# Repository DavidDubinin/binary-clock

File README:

# BINARY CLOCK AVR CODE - ATMEGA48

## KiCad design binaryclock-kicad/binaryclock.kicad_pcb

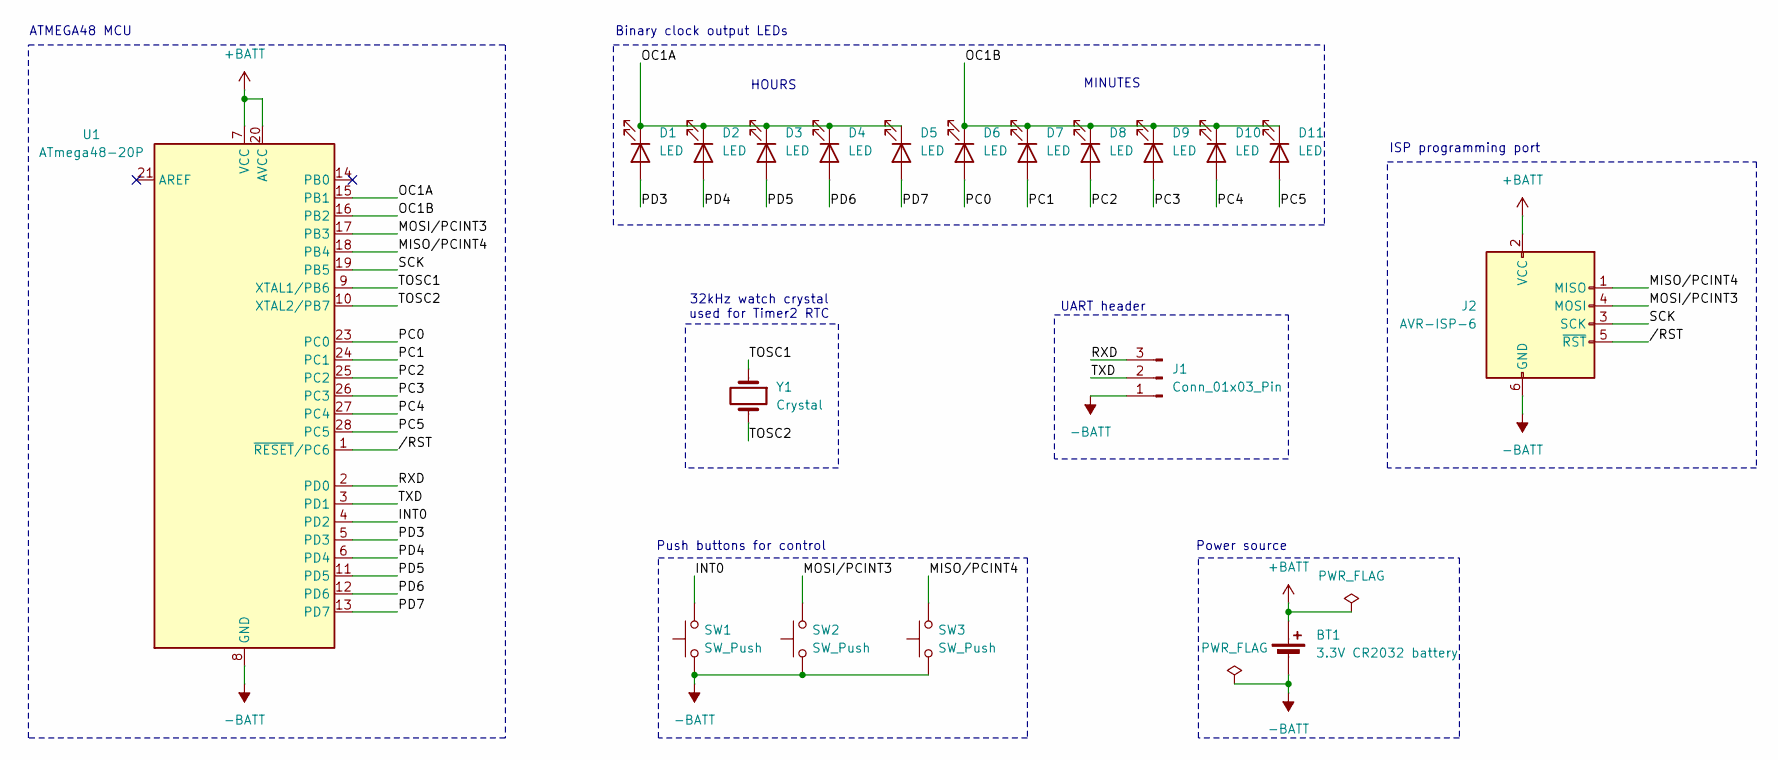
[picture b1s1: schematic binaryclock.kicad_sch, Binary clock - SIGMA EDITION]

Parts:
BT1: 3.3V CR2032 battery; BatteryHolder_Keystone_103_1x20mm
D1, D2, D3, D4, D5, D6, D7, D8, D9, D10, D11: LED; LED_D3.0mm
J1: Conn_01x03_Pin; PinHeader_1x03_P2.54mm_Vertical
J2: AVR-ISP-6; IDC-Header_2x03_P2.54mm_Vertical
SW1, SW2, SW3: SW_Push; SW_PUSH_6mm
U1: ATmega48-20P; DIP-28_W7.62mm_Socket_LongPads
Y1: Crystal; PinHeader_1x02_P2.54mm_Vertical

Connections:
+BATT: BT1.1 (+), J2.2 (VCC), U1.7 (VCC), U1.20 (AVCC)
-BATT: BT1.2 (-), J1.1, J2.6 (GND), SW1.1, SW2.1, SW3.1, U1.8 (GND), U1.22 (GND)
/INT0: SW1.2, U1.4 (PD2)
/MISO/PCINT4: J2.1 (MISO), SW3.2, U1.18 (PB4)
/MOSI/PCINT3: J2.4 (MOSI), SW2.2, U1.17 (PB3)
/OC1A: D1.1 (K), D2.1 (K), D3.1 (K), D4.1 (K), D5.1 (K), U1.15 (PB1)
/OC1B: D6.1 (K), D7.1 (K), D8.1 (K), D9.1 (K), D10.1 (K), D11.1 (K), U1.16 (PB2)
/PC0: D6.2 (A), U1.23 (PC0)
/PC1: D7.2 (A), U1.24 (PC1)
/PC2: D8.2 (A), U1.25 (PC2)
/PC3: D9.2 (A), U1.26 (PC3)
/PC4: D10.2 (A), U1.27 (PC4)
/PC5: D11.2 (A), U1.28 (PC5)
/PD3: D1.2 (A), U1.5 (PD3)
/PD4: D2.2 (A), U1.6 (PD4)
/PD5: D3.2 (A), U1.11 (PD5)
/PD6: D4.2 (A), U1.12 (PD6)
/PD7: D5.2 (A), U1.13 (PD7)
/RXD: J1.3, U1.2 (PD0)
/SCK: J2.3 (SCK), U1.19 (PB5)
/TOSC1: U1.9 (XTAL1/PB6), Y1.1
/TOSC2: U1.10 (XTAL2/PB7), Y1.2
/TXD: J1.2, U1.3 (PD1)
//RST: J2.5 (~RST), U1.1 (~RESET/PC6)

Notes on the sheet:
UART header
Push buttons for control
Power source
ISP programming port
32kHz watch crystal used for Timer2 RTC
HOURS
Binary clock output LEDs
MINUTES
ATMEGA48 MCU

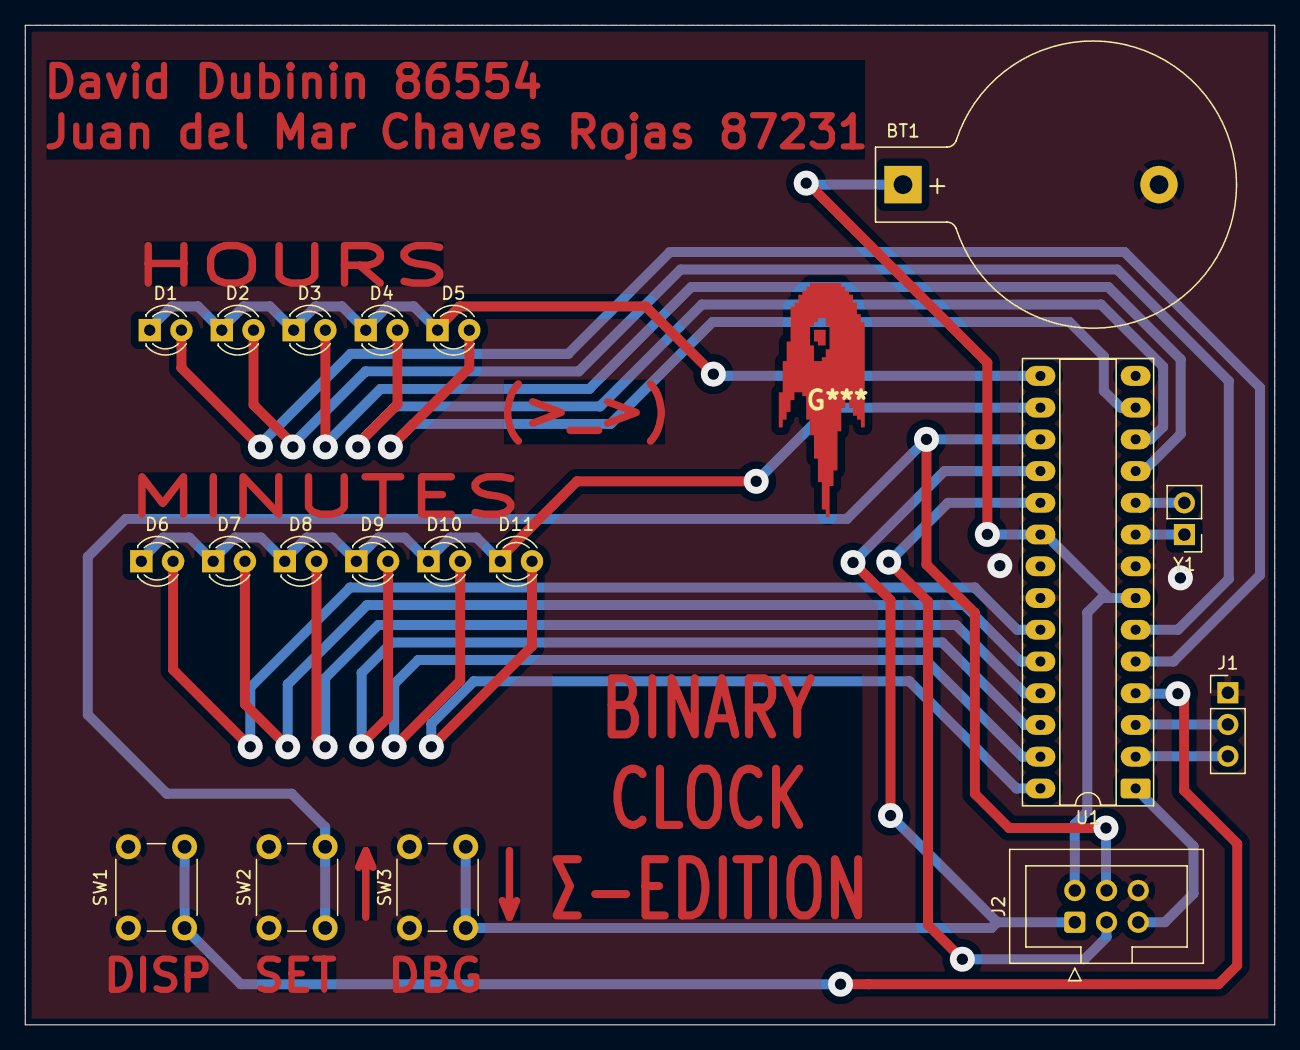
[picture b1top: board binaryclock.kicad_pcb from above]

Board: 2 copper layers, 100.0 x 80.0 mm, 19 parts (0 on the bottom side), 24 nets.

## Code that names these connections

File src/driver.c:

#include "driver.h"
#include <avr/interrupt.h>

#include <util/atomic.h>

void initLeds(void) {
    DDRD |= (1 << PD3) | (1 << PD4) | (1 << PD5) | (1 << PD6) | (1 << PD7); // Stundenpins, 5 bit
    DDRC |= (1 << PC0) | (1 << PC1) | (1 << PC2) | (1 << PC3) | (1 << PC4) | (1 << PC5); // Minutenpins, 6 bit
}

void disableLeds(void){
    PORTD &= ~(1 << PD3) & ~(1 << PD4) & ~(1 << PD5) & ~(1 << PD6) & ~(1 << PD7); // Stundenpins, 5 bit
    PORTC &= ~(1 << PC0) & ~(1 << PC1) & ~(1 << PC2) & ~(1 << PC3) & ~(1 << PC4) & ~(1 << PC5); // Minutenpins, 6 bit
}

void initButtons(void) {
    //set Button pins as inputs
    DDRD &= ~(1 << PD2);
    DDRB &= ~(1 << PB3) & ~(1 << PB4);
    //enable internal pullups for Buttons
    PORTD |= (1 << PD2);
    PORTB |= (1 << PB3) | (1 << PB4);

    //set INT0 trigger to falling edge
    EICRA |= (1 << ISC01);
    EICRA &= ~(1 << ISC00);
    //Enable INT0
    EIMSK |= (1 << INT0);

    //Enable PCINT7..0 interrupt und Maske for PCINT3..4
    PCICR |= (1 << PCIE0);
    PCMSK0 |= (1 << PCINT3) | (1 << PCINT4);
}
 
void initPwm(void) {
    DDRB |= (1 << DDB1) | (1 << DDB2); // OC1A/PB1 bzw OC1B/PB2 auf Output für Stunden/Minuten

    TCCR1A |= (1 << WGM10) | (1 << WGM11) | (1 << COM1A1) 
            | (1 << COM1B1) | (1 << COM1A0) | (1 << COM1B0);
            
    TCCR1B |= (1 << WGM12) | (1 << CS10);
    TCCR1B &= ~(1 << WGM13) & ~(1 << CS11) & ~(1 << CS12);

    OCR1A = (1023 * DUTY_CYCLE) / 100;
    OCR1B = (1023 * DUTY_CYCLE) / 100;
}

//Watch Crystal 32 768 Hz, Prescaler 128, F_OCnx = 1/2 Hz (1 interrupt per sec) => OCRnx = 255  
//Toggle OC2A on Compare Match, CTC Mode, TOP=OCR2A
void initQuartz_seconds(void){
    //1. Disable the Timer/Counter2 interrupts by clearing OCIE2x and TOIE2
    TIMSK2 &= ~(1<<OCIE2A) & ~(1<<OCIE2B) & ~(1<<TOIE2);

    //2. Select clock source by setting AS2 as appropriate
    //Enable Asynchronous Timer/Counter2
    ASSR |= (1 << AS2);

    //3. Write new values to TCNT2, OCR2x, and TCCR2x.
    //Toggle OC2A on Compare Match

    TCNT2 = 0x00; //reset timer
    TCCR2A |= (1 << COM2A0);
    TCCR2A &= ~(1 << COM2A1);

    //CTC-Mode
    TCCR2A |= (1 << WGM21);
    TCCR2A &= ~(1 << WGM20);
    TCCR2B &= ~(1 << WGM22);

    //CS selection mit Prescaler = 128
    TCCR2B |= (1 << CS20) | (1 << CS22);
    TCCR2B &= ~(1 << CS21);

    //Compare Match bei Timer = 255 => OC2A Interrupt Flag Set
    OCR2A = 0xFF;

    //4. To switch to asynchronous operation: Wait for TCN2xUB, OCR2xUB, and TCR2xUB
    //ASSR = xxx1 1111 BAD
    //ASSR = xxx0 0000
    while(ASSR & ((1<<TCN2UB) | (1<<OCR2AUB) | (1<<OCR2BUB) | (1<<TCR2AUB) | (1<<TCR2BUB))){
    __builtin_avr_nop(); // sigma approved!!!
    }

    //5. Clear the Timer/Counter2 Interrupt Flags
    TIFR2 |= (1 << OCF2B) | (1 << OCF2A) | (1 << TOV2);

    //6. Enable interrupts, if needed
    //Enable Output Compare Match Interrupt A
    TIMSK2 |= (1 << OCIE2A);
}



//Watch Crystal 32 768 Hz, Prescaler 1, F_OCnx = 512Hz (1 interrupt per ms) => OCRnx = 31  
//Toggle OC2A on Compare Match, CTC Mode, TOP=OCR2A

// F_OCnx = F_clkIO / (2 * N * (1 + OCRnx))
// F_Interrupt = 2 * F_OCnx (2x Interrupts in einer Periode CTC)
// F_interrupt = 2 * ( F_clkIO / (2 * N * (1 + OCRnx)) )
// F_interrupt = 2 * ( 32 768Hz / (2 * 1 * (1 + OCRnx)) )
// F_interrupt = 2 * ( 32 768Hz / (2 * 1 * (1 + 63)) ) = 512Hz F_Interrupts ↯ wollen aber 1024Hz 


// Gleichung
// 1024 Hz = 32 768Hz / (1*(1 + OCRnx))          | * 1*(1+OCRnx)
// 1024 Hz * (1 + OCRnx) = 32 768 Hz             | / 1024
// 1 + OCRnx = 32 768 Hz / 1024 Hz
// 1 + OCRnx = 32                                | - 1
// OCRnx = 31 bei 1024 Iterrupts/s

void initQuartz_ms(void){
    //1. Disable the Timer/Counter2 interrupts by clearing OCIE2x and TOIE2
    TIMSK2 &= ~(1<<OCIE2A) & ~(1<<OCIE2B) & ~(1<<TOIE2);

    //2. Select clock source by setting AS2 as appropriate
    //Enable Asynchronous Timer/Counter2
    ASSR |= (1 << AS2);

    //3. Write new values to TCNT2, OCR2x, and TCCR2x.
    //Toggle OC2A on Compare Match

    TCNT2 = 0x00; //reset timer
    TCCR2A |= (1 << COM2A0);
    TCCR2A &= ~(1 << COM2A1);

    //CTC-Mode
    TCCR2A |= (1 << WGM21);
    TCCR2A &= ~(1 << WGM20);
    TCCR2B &= ~(1 << WGM22);

    //CS selection mit Prescaler = 1 (= No prescaler)
    TCCR2B |= (1 << CS20);
    TCCR2B &= ~(1 << CS22) & ~(1 << CS21);

    //Compare Match bei Timer = 31 => OC2A Interrupt Flag Set | siehe Rechnung oben
    OCR2A = 31;

    //4. To switch to asynchronous operation: Wait for TCN2xUB, OCR2xUB, and TCR2xUB
    //ASSR = xxx1 1111 BAD
    //ASSR = xxx0 0000
    while(ASSR & ((1<<TCN2UB) | (1<<OCR2AUB) | (1<<OCR2BUB) | (1<<TCR2AUB) | (1<<TCR2BUB))){
    __builtin_avr_nop(); // sigma approved!!!
    }

    //5. Clear the Timer/Counter2 Interrupt Flags
    TIFR2 |= (1 << OCF2B) | (1 << OCF2A) | (1 << TOV2);

    //6. Enable interrupts, if needed
    //Enable Output Compare Match Interrupt A
    TIMSK2 |= (1 << OCIE2A);
}


void setLeds(uint8_t hourLedsVal, uint8_t minuteLedsVal) {
    ATOMIC_BLOCK(ATOMIC_RESTORESTATE){
        PORTD = __builtin_avr_insert_bits(0x01234FFF, hourLedsVal, PORTD); // portd 7 bis 3  stunden
        PORTC = __builtin_avr_insert_bits(0xFF012345, minuteLedsVal, PORTC); //portc 5 bis 0 Sekunden
    }
}

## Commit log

2025-12-17 added kicad stuff
2025-12-18 added make.sh
2025-12-18 assigned footprints to components
2025-12-18 updated schematic svg
2025-12-20 updated .gitignore
2025-12-26 initial pcb draft
2025-12-26 passed drc
2025-12-26 idk what i did
2025-12-28 prettified pcb
2025-12-29 did some adjustments
2025-12-31 created fabrication files
2025-12-31 wip pcb test
2026-01-01 NOTHING IS WORKING (YET)
2026-01-06 pcb finalized
2026-01-07 finished pcb
2026-01-07 TRUE FINAL PCB VERSION
2026-01-20 updated code
2026-03-03 pwm implemented, wip led setup
2026-03-04 delay based timing works!!
2026-03-04 small changes
2026-03-04 watch crystal based timing works!!!!
2026-03-04 fixed kicad project file
2026-03-04 did shit
2026-03-06 wip buttons
2026-03-11 fix README.md
2026-03-11 implemented debounce
2026-03-11 DISP show seconds muahahaha
2026-03-13 started work on controls
2026-03-13 fixed shit
2026-03-14 wip buttonshit?! lampenzeug
2026-03-14 WIP RESTRUCTURE
2026-03-16 finished time.h/time.c
2026-03-16 wip state.h
2026-03-17 worked on states wip fast fertig sigma
2026-03-17 tried to implement millis
2026-03-18 finished millisecond-based timebase, reworked rebounce, moved state logic out of time.c
2026-03-18 implemented needed ATOMIC_BLOCKS
2026-03-19 WIP sleepmode
2026-03-19 finished sleepMode
2026-03-20 uart doesnt work!! :D
2026-03-20 UART DOESNT WORK
2026-03-21 finished GET time
2026-03-21 finished uart
2026-03-22 finished and polished
